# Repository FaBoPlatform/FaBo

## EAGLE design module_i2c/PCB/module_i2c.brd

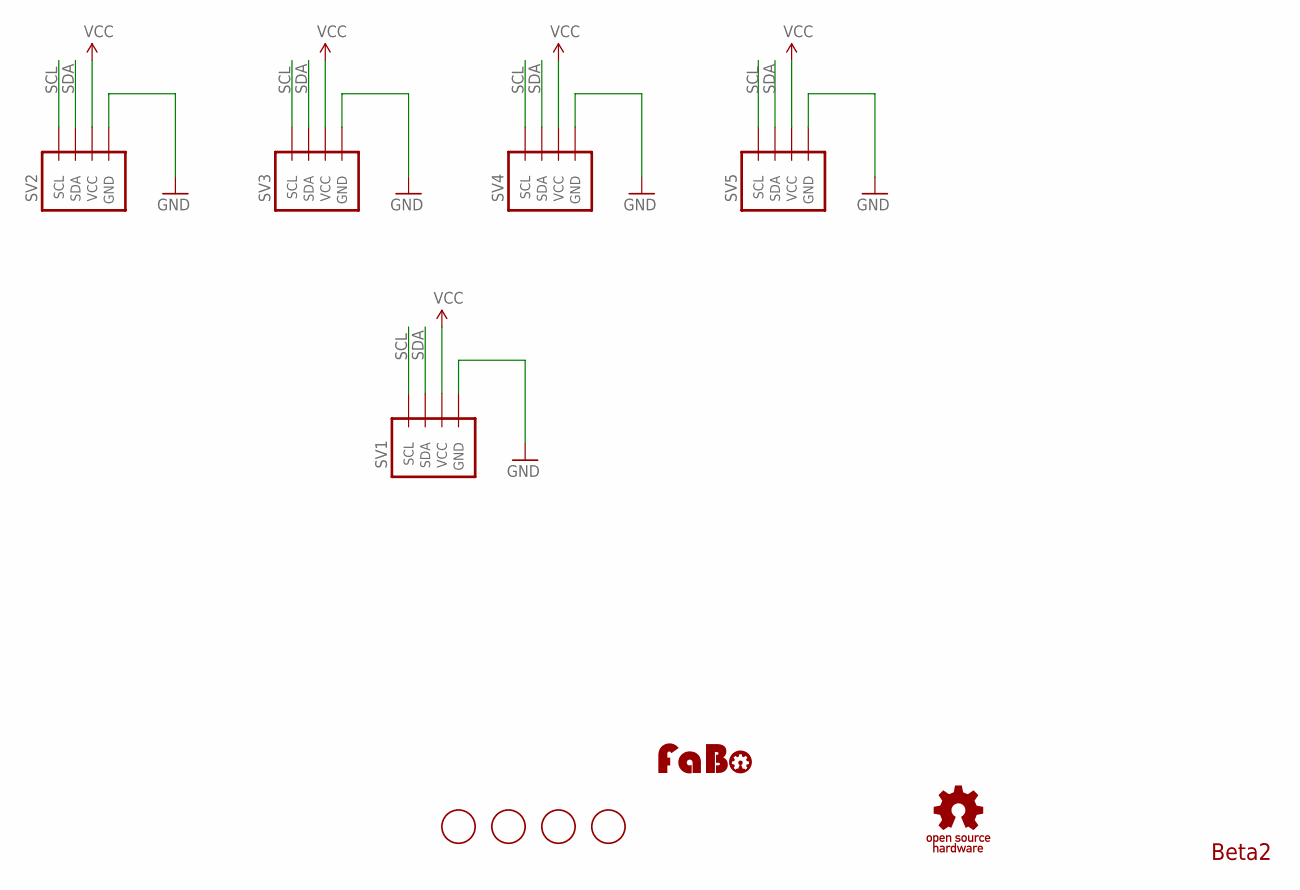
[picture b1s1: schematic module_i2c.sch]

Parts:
SV1, SV2, SV3, SV4, SV5: BRICK_I2C_CONNECTOR
U$7, U$8, U$9, U$10: SCREW-PAD-3MM; SCREWPAD_3MM
U$11: LOGO_FABO-M; LOGO_FABO_M
U$12: LOGO_OSHW_T-M; LOGO_OSHW_T_M

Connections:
GND: SV1.GND, SV2.GND, SV3.GND, SV4.GND, SV5.GND
SCL: SV1.SCL, SV2.SCL, SV3.SCL, SV4.SCL, SV5.SCL
SDA: SV1.SDA, SV2.SDA, SV3.SDA, SV4.SDA, SV5.SDA
VCC: SV1.VCC, SV2.VCC, SV3.VCC, SV4.VCC, SV5.VCC

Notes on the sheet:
Beta2

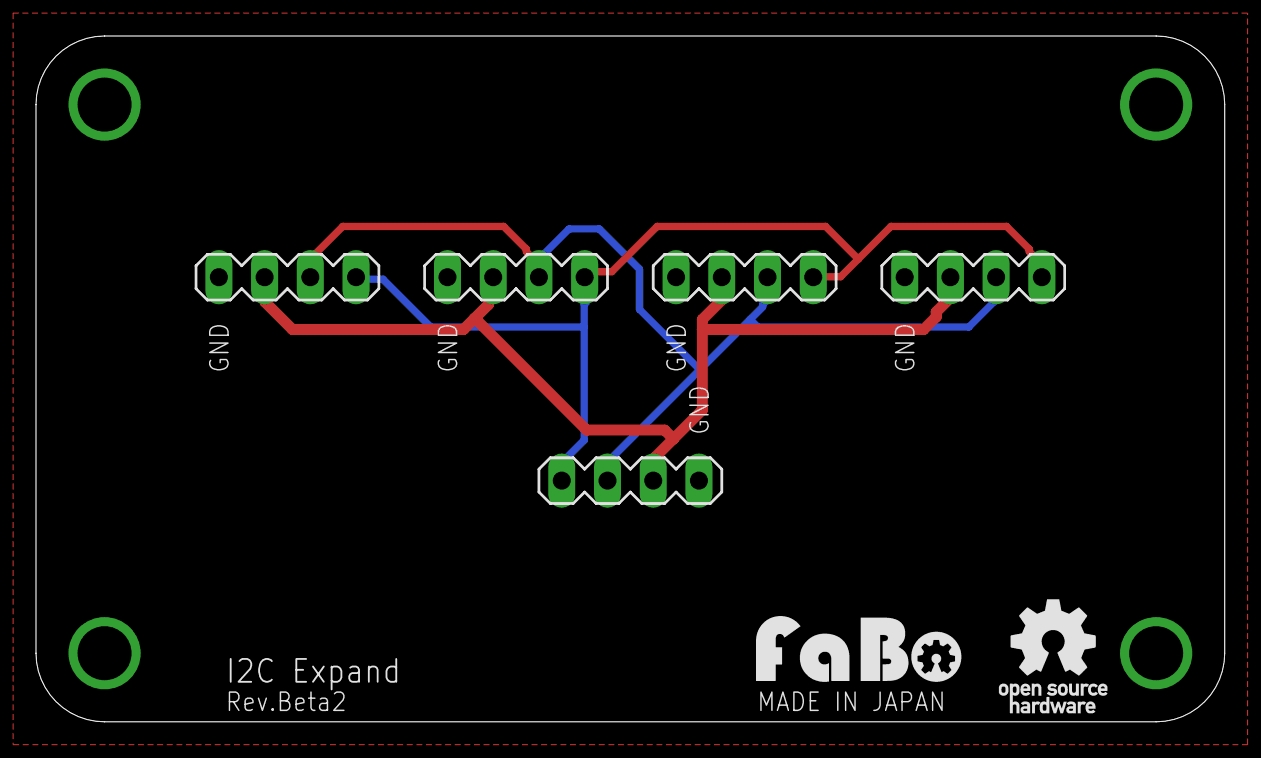
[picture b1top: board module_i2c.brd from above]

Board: 2 copper layers, 66.0 x 38.1 mm, 11 parts (0 on the bottom side), 4 nets.

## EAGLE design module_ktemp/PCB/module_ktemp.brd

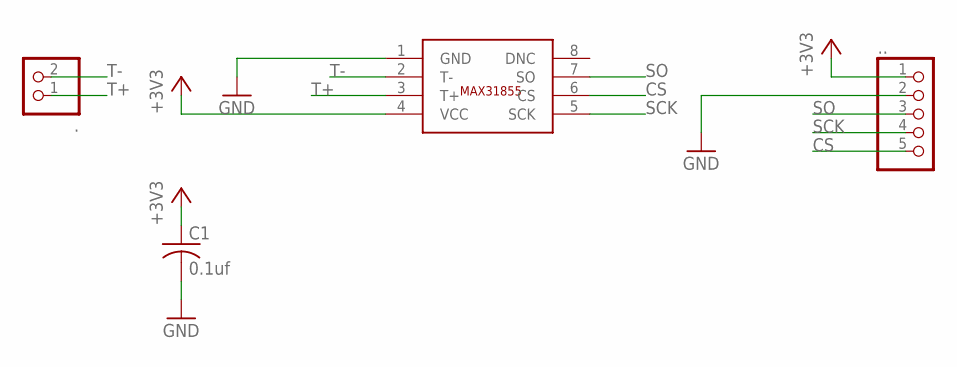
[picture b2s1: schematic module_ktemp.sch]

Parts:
.: PINHD-1X2; 1X02
..: PINHD-1X5; 1X05
C1: 0.1uf; C0603
U$2: MAXIM-MAX31855

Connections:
+3V3: ...1, C1.1, U$2.4 (VCC)
CS: ...5, U$2.6 (CS)
GND: ...2, C1.2, U$2.1 (GND)
SCK: ...4, U$2.5 (SCK)
SO: ...3, U$2.7 (SO)
T+: ..1, U$2.3 (T+)
T-: ..2, U$2.2 (T-)

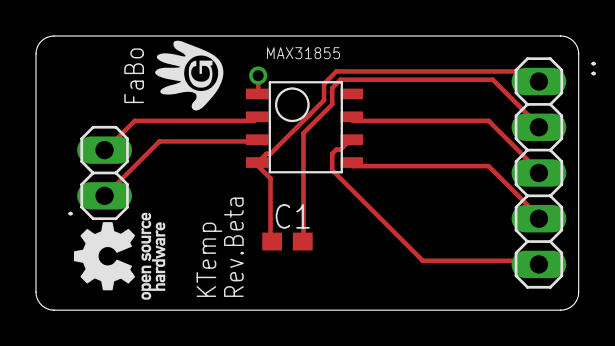
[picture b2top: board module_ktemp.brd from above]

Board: 2 copper layers, 30.1 x 15.2 mm, 6 parts (0 on the bottom side), 7 nets.

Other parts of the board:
U$3: LOGO_OSHW_T_M
U$4: LOGO_FABO_M

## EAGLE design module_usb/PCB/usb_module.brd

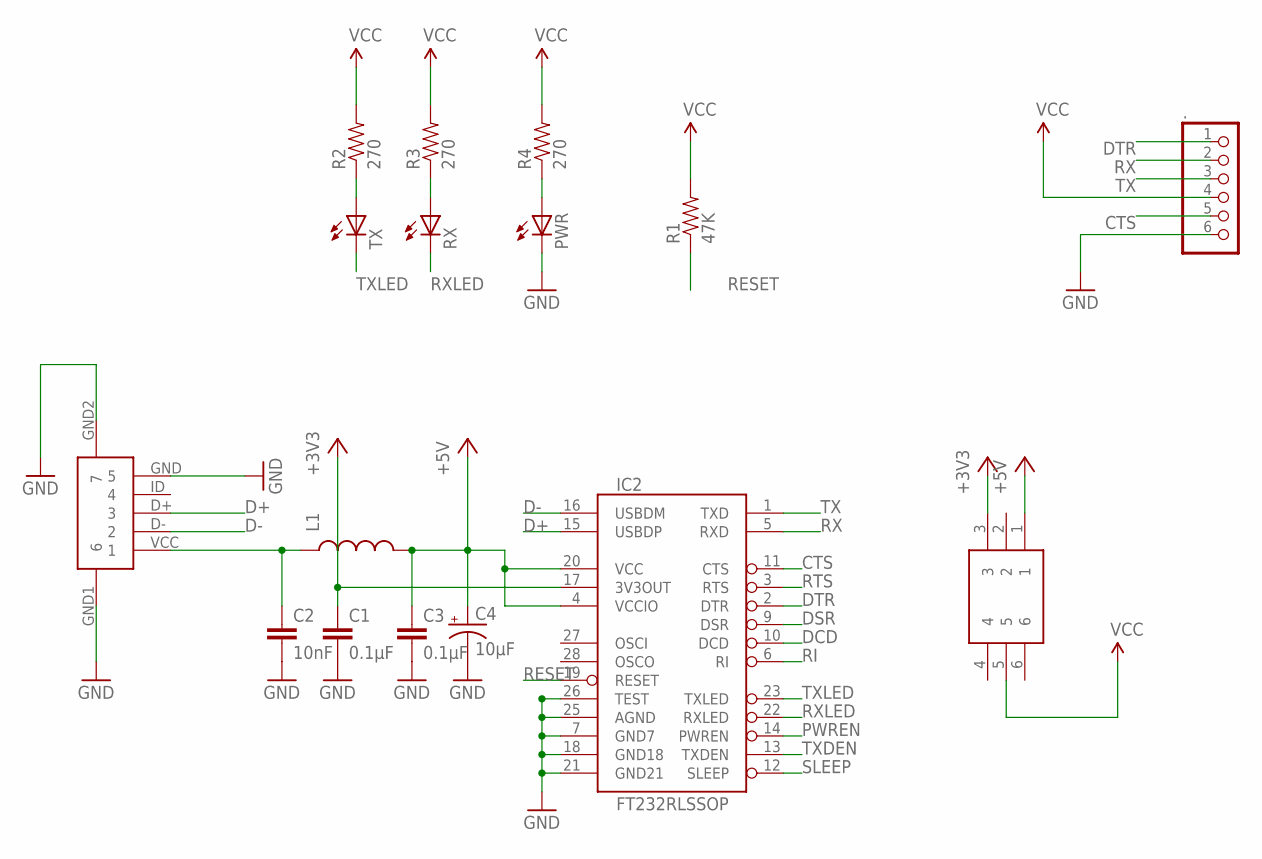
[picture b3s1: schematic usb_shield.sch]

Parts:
.: PINHD-1X6; 1X06
C1, C3: 0.1μF; 0603-CAP
C2: 10nF; 0603-CAP
C4: 10μF; EIA3216
IC2: FT232RLSSOP; SSOP28DB
L1: INDUCTOR0603; 0603
PWR: LEDCHIP-LED0805; CHIP-LED0805
R1: 47K; 0603-RES
R2, R3, R4: 270; 0603-RES
RX: LEDCHIP-LED0805; CHIP-LED0805
TX: LEDCHIP-LED0805; CHIP-LED0805
U$1: USB-MICRO-B-FEMALE
U$2: C&K_JS202011SCQN

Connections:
+3V3: C1.1, IC2.17 (3V3OUT), U$2.3
+5V: C3.1, C4.A (+), IC2.4 (VCCIO), IC2.20 (VCC), L1.2, U$2.1
CTS: ..5, IC2.11 (CTS)
D+: IC2.15 (USBDP), U$1.D+ (3)
D-: IC2.16 (USBDM), U$1.D- (2)
DCD: IC2.10 (DCD)
DSR: IC2.9 (DSR)
DTR: ..1, IC2.2 (DTR)
GND: ..6, C1.2, C2.2, C3.2, C4.C (-), IC2.7 (GND7), IC2.18 (GND18), IC2.21 (GND21), IC2.25 (AGND), IC2.26 (TEST), PWR.C, U$1.GND (5), U$1.GND1 (6), U$1.GND2 (7)
unnamed: C2.1, L1.1, U$1.VCC (1)
unnamed: R2.1, TX.A
unnamed: R3.1, RX.A
unnamed: PWR.A, R4.1
PWREN: IC2.14 (PWREN)
RESET: IC2.19 (RESET), R1.1
RI: IC2.6 (RI)
RTS: IC2.3 (RTS)
RX: ..2, IC2.5 (RXD)
RXLED: IC2.22 (RXLED), RX.C
SLEEP: IC2.12 (SLEEP)
TX: ..3, IC2.1 (TXD)
TXDEN: IC2.13 (TXDEN)
TXLED: IC2.23 (TXLED), TX.C
VCC: ..4, R1.2, R2.2, R3.2, R4.2, U$2.5

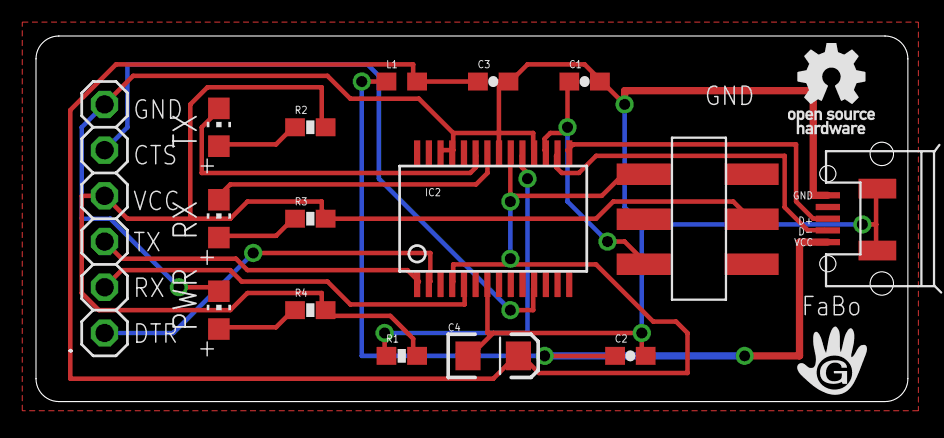
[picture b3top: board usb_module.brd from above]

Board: 2 copper layers, 48.4 x 20.3 mm, 18 parts (0 on the bottom side), 17 nets.

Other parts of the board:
U$3: LOGO_OSHW_T_M
U$4: LOGO_FABO_M

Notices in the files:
parts and their libraries:
SparkFun: Licensing: CC v3.0 Share-Alike You are welcome to use this library for commercial purposes.
